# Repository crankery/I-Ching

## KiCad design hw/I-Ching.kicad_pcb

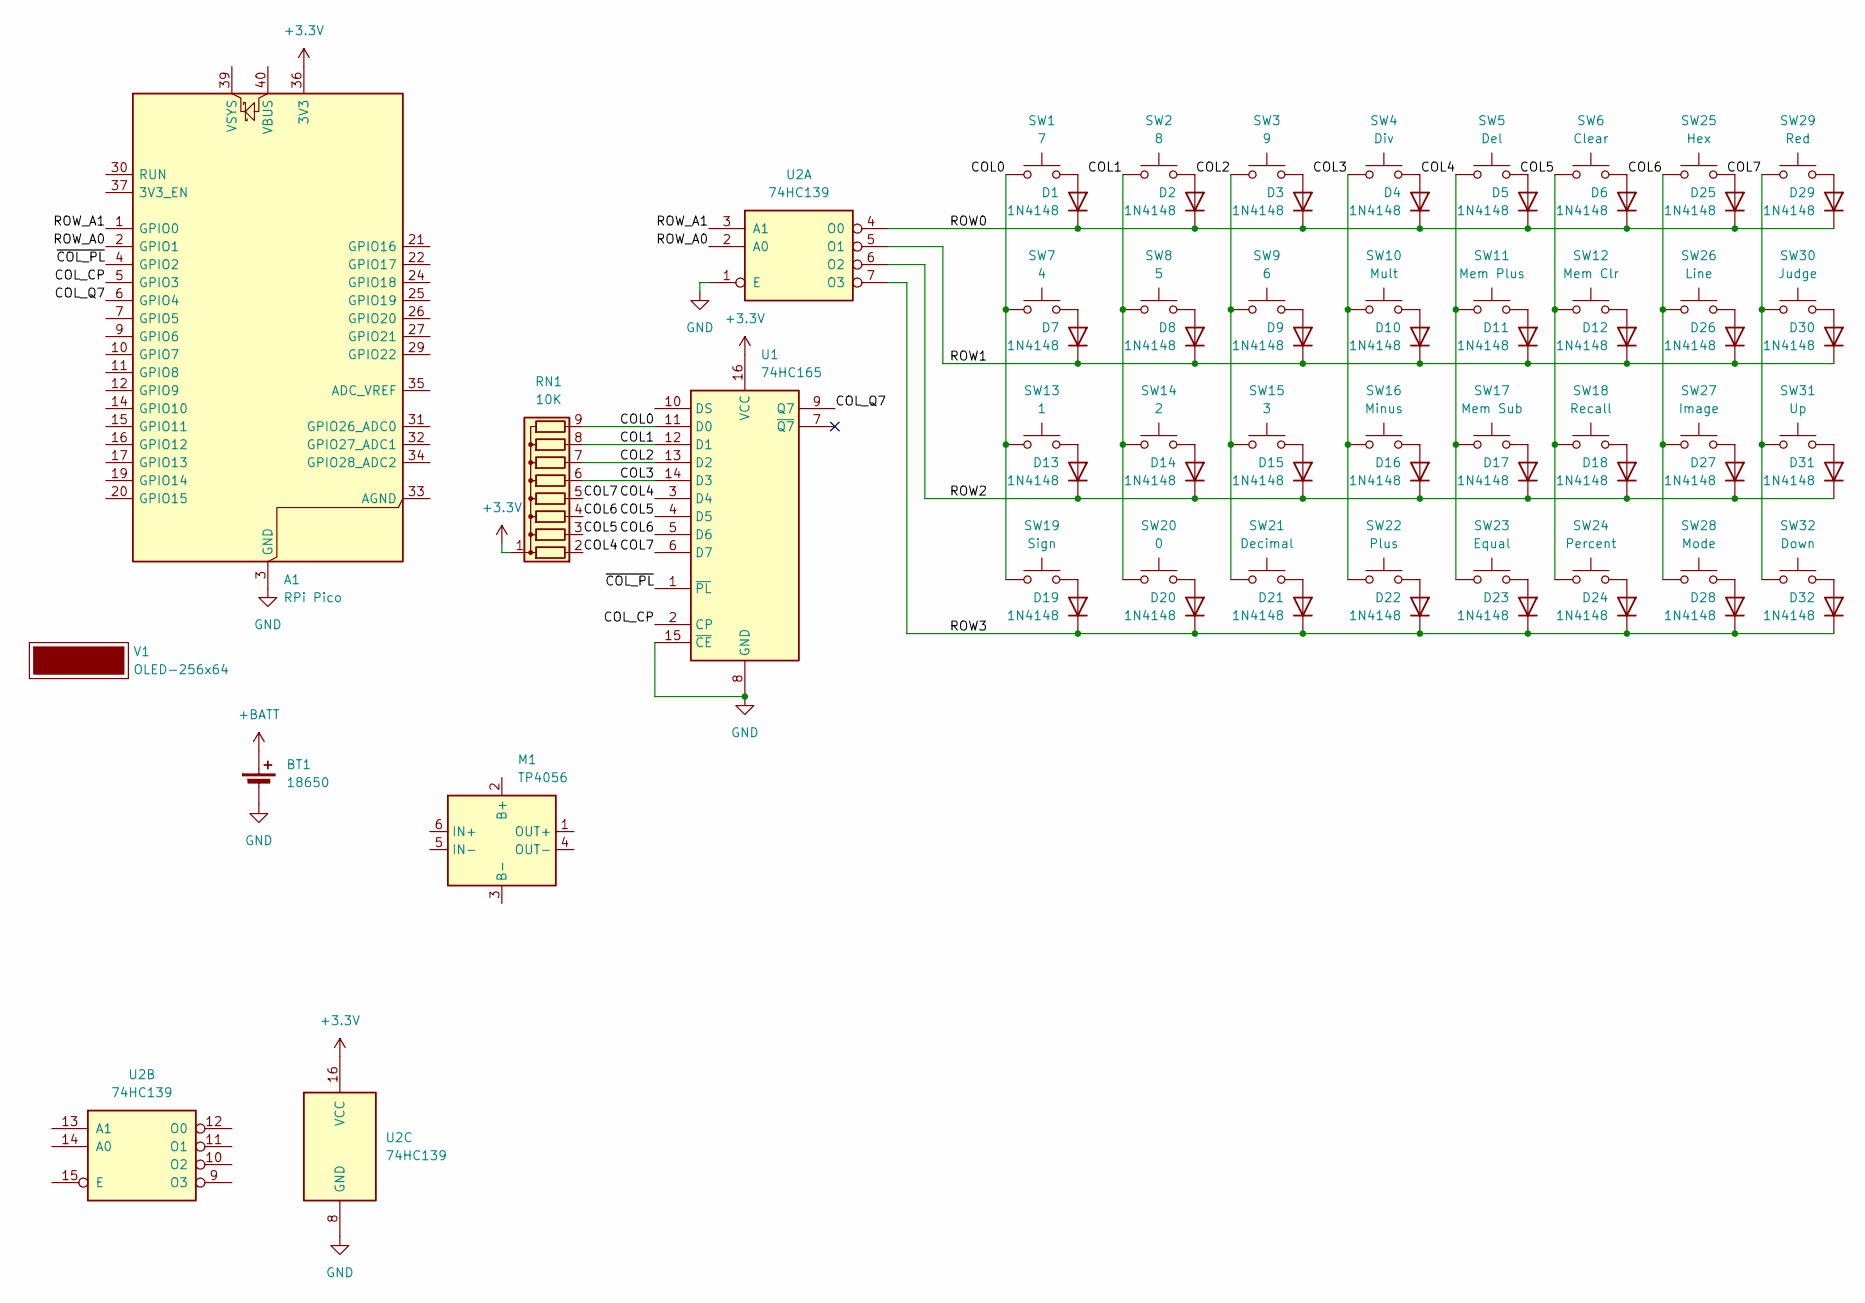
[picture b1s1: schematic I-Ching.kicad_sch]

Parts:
A1: RPi Pico; RaspberryPi_Pico_SMD
BT1: 18650; JST_PH_S2B-PH-K_1x02_P2.00mm_Horizontal
D1, D2, D3, D4, D5, D6, D7, D8, D9, D10, D11, D12, D13, D14, D15, D16, D17, D18, D19, D20, D21, D22, D23, D24, D25, D26, D27, D28, D29, D30, D31, D32: 1N4148; D_DO-35_SOD27_P7.62mm_Horizontal
M1: TP4056; TP4056_Module
RN1: 10K; R_Array_SIP9
SW1: 7; SW_PUSH-12mm
SW2: 8; SW_PUSH-12mm
SW3: 9; SW_PUSH-12mm
SW4: Div; SW_PUSH-12mm
SW5: Del; SW_PUSH-12mm
SW6: Clear; SW_PUSH-12mm
SW7: 4; SW_PUSH-12mm
SW8: 5; SW_PUSH-12mm
SW9: 6; SW_PUSH-12mm
SW10: Mult; SW_PUSH-12mm
SW11: Mem Plus; SW_PUSH-12mm
SW12: Mem Clr; SW_PUSH-12mm
SW13: 1; SW_PUSH-12mm
SW14: 2; SW_PUSH-12mm
SW15: 3; SW_PUSH-12mm
SW16: Minus; SW_PUSH-12mm
SW17: Mem Sub; SW_PUSH-12mm
SW18: Recall; SW_PUSH-12mm
SW19: Sign; SW_PUSH-12mm
SW20: 0; SW_PUSH-12mm
SW21: Decimal; SW_PUSH-12mm
SW22: Plus; SW_PUSH-12mm
SW23: Equal; SW_PUSH-12mm
SW24: Percent; SW_PUSH-12mm
SW25: Hex; SW_PUSH-12mm
SW26: Line; SW_PUSH-12mm
SW27: Image; SW_PUSH-12mm
SW28: Mode; SW_PUSH-12mm
SW29: Red; SW_PUSH-12mm
SW30: Judge; SW_PUSH-12mm
SW31: Up; SW_PUSH-12mm
SW32: Down; SW_PUSH-12mm
U1: 74HC165; DIP-16_W7.62mm
U2: 74HC139; DIP-16_W7.62mm
V1: OLED-256x64; Display

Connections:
+3.3V: A1.36 (3V3), RN1.1 (common), U1.16 (VCC), U2.16 (VCC)
+BATT: BT1.1 (+)
/COL0: RN1.9 (R8), SW1.1, SW7.1, SW13.1, SW19.1, U1.11 (D0)
/COL1: RN1.8 (R7), SW2.1, SW8.1, SW14.1, SW20.1, U1.12 (D1)
/COL2: RN1.7 (R6), SW3.1, SW9.1, SW15.1, SW21.1, U1.13 (D2)
/COL3: RN1.6 (R5), SW4.1, SW10.1, SW16.1, SW22.1, U1.14 (D3)
/COL4: RN1.2 (R1), SW5.1, SW11.1, SW17.1, SW23.1, U1.3 (D4)
/COL5: RN1.3 (R2), SW6.1, SW12.1, SW18.1, SW24.1, U1.4 (D5)
/COL6: RN1.4 (R3), SW25.1, SW26.1, SW27.1, SW28.1, U1.5 (D6)
/COL7: RN1.5 (R4), SW29.1, SW30.1, SW31.1, SW32.1, U1.6 (D7)
/COL_CP: A1.5 (GPIO3), U1.2 (CP)
/COL_Q7: A1.6 (GPIO4), U1.9 (Q7)
/ROW0: D1.1 (K), D2.1 (K), D3.1 (K), D4.1 (K), D5.1 (K), D6.1 (K), D25.1 (K), D29.1 (K), U2.4 (O0)
/ROW1: D7.1 (K), D8.1 (K), D9.1 (K), D10.1 (K), D11.1 (K), D12.1 (K), D26.1 (K), D30.1 (K), U2.5 (O1)
/ROW2: D13.1 (K), D14.1 (K), D15.1 (K), D16.1 (K), D17.1 (K), D18.1 (K), D27.1 (K), D31.1 (K), U2.6 (O2)
/ROW3: D19.1 (K), D20.1 (K), D21.1 (K), D22.1 (K), D23.1 (K), D24.1 (K), D28.1 (K), D32.1 (K), U2.7 (O3)
/ROW_A0: A1.2 (GPIO1), U2.2 (A0)
/ROW_A1: A1.1 (GPIO0), U2.3 (A1)
/~COL_PL: A1.4 (GPIO2), U1.1 (~PL)
GND: A1.3 (GND), A1.8 (GND), A1.13 (GND), A1.18 (GND), A1.23 (GND), A1.28 (GND), A1.38 (GND), BT1.2 (-), U1.8 (GND), U1.15 (~CE), U2.1 (E), U2.8 (GND)
unnamed: D1.2 (A), SW1.2
unnamed: D2.2 (A), SW2.2
unnamed: D3.2 (A), SW3.2
unnamed: D4.2 (A), SW4.2
unnamed: D5.2 (A), SW5.2
unnamed: D6.2 (A), SW6.2
unnamed: D7.2 (A), SW7.2
unnamed: D8.2 (A), SW8.2
unnamed: D9.2 (A), SW9.2
unnamed: D10.2 (A), SW10.2
unnamed: D11.2 (A), SW11.2
unnamed: D12.2 (A), SW12.2
unnamed: D13.2 (A), SW13.2
unnamed: D14.2 (A), SW14.2
unnamed: D15.2 (A), SW15.2
unnamed: D16.2 (A), SW16.2
unnamed: D17.2 (A), SW17.2
unnamed: D18.2 (A), SW18.2
unnamed: D19.2 (A), SW19.2
unnamed: D20.2 (A), SW20.2
unnamed: D21.2 (A), SW21.2
unnamed: D22.2 (A), SW22.2
unnamed: D23.2 (A), SW23.2
unnamed: D24.2 (A), SW24.2
unnamed: D25.2 (A), SW25.2
unnamed: D26.2 (A), SW26.2
unnamed: D27.2 (A), SW27.2
unnamed: D28.2 (A), SW28.2
unnamed: D29.2 (A), SW29.2
unnamed: D30.2 (A), SW30.2
unnamed: D31.2 (A), SW31.2
unnamed: D32.2 (A), SW32.2

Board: 2 copper layers, 71 parts (0 on the bottom side), 51 nets, no tracks yet.
